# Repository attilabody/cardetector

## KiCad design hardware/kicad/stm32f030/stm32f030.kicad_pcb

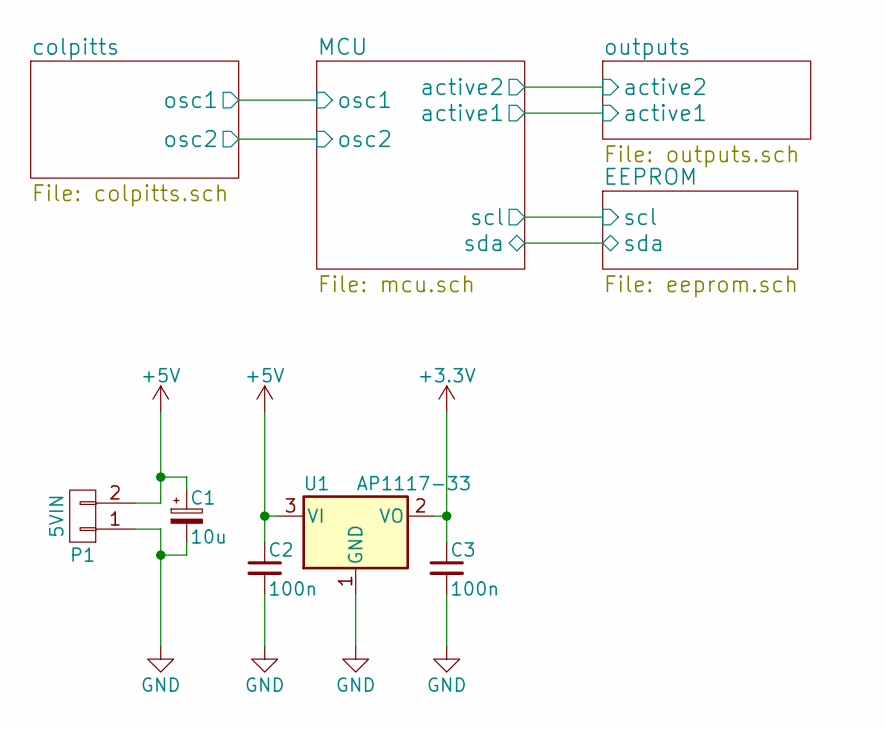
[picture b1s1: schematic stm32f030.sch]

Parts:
C1: 10u; Tantalum_Case-B_EIA-3528-21_Hand
C2, C3: 100n; C_0805_HandSoldering
P1: 5VIN; bornier2
U1: AP1117-33; SOT-223-3Lead_TabPin2

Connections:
+3V3: C3.1, U1.2 (VO); also elsewhere on the board
+5V: C1.1, C2.1, P1.2, U1.3 (VI); also elsewhere on the board
GND: C1.2, C2.2, C3.2, P1.1, U1.1 (GND); also elsewhere on the board

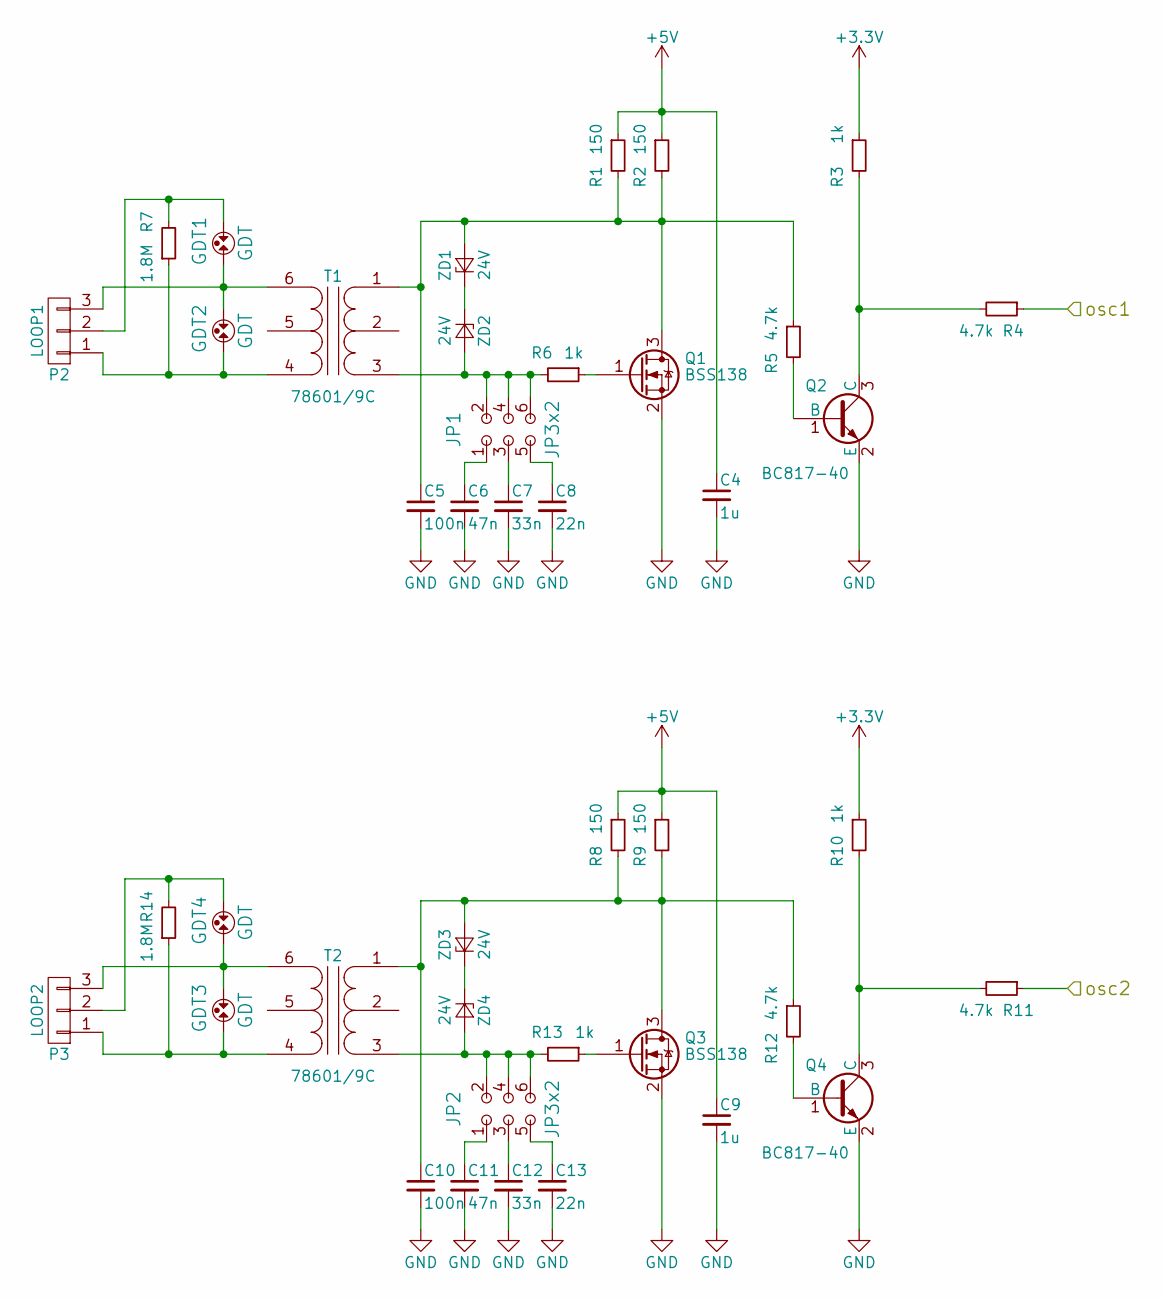
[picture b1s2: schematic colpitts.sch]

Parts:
C4, C9: 1u; C_1206_HandSoldering
C5, C10: 100n; C_1206_HandSoldering
C6, C11: 47n; C_1206
C7, C12: 33n; C_0805_HandSoldering
C8, C13: 22n; C_0805_HandSoldering
GDT1, GDT2, GDT3, GDT4: GDT
JP1, JP2: JP3x2; Pin_Header_Straight_2x03_Pitch2.54mm
P2: LOOP1; bornier3
P3: LOOP2; bornier3
Q1, Q3: BSS138; SOT-23
Q2, Q4: BC817-40; SOT-23
R1, R2, R8, R9: 150; R_0805
R3, R6, R10, R13: 1k; R_0603_HandSoldering
R4, R5, R11, R12: 4.7k; R_0603_HandSoldering
R7, R14: 1.8M; R_0603_HandSoldering
T1, T2: 78601/9C; Murata_Impulse_Transformer
ZD1, ZD2, ZD3, ZD4: 24V; D_MiniMELF_Standard

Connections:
+3V3: R3.1, R10.1; also elsewhere on the board
+5V: C4.1, C9.1, R1.1, R2.1, R8.1, R9.1; also elsewhere on the board
/MCU/osc1: R4.1; also elsewhere on the board
/MCU/osc2: R11.1; also elsewhere on the board
GND: C4.2, C5.2, C6.2, C7.2, C8.2, C9.2, C10.2, C11.2, C12.2, C13.2, Q1.2 (S), Q2.2 (E), Q3.2 (S), Q4.2 (E); also elsewhere on the board
unnamed: C5.1, Q1.3 (D), R1.2, R2.2, R5.1, T1.1 (AA), ZD1.2 (A)
unnamed: C6.1, JP1.1
unnamed: C7.1, JP1.3
unnamed: C8.1, JP1.5
unnamed: C10.1, Q3.3 (D), R8.2, R9.2, R12.1, T2.1 (AA), ZD3.2 (A)
unnamed: C11.1, JP2.1
unnamed: C12.1, JP2.3
unnamed: C13.1, JP2.5
unnamed: GDT1.1, GDT2.2, P2.3, T1.6 (SB)
unnamed: GDT1.2, P2.2, R7.2
unnamed: GDT2.1, P2.1, R7.1, T1.4 (SA)
unnamed: GDT3.1, P3.1, R14.1, T2.4 (SA)
unnamed: GDT3.2, GDT4.1, P3.3, T2.6 (SB)
unnamed: GDT4.2, P3.2, R14.2
unnamed: JP1.2, JP1.4, JP1.6, R6.2, T1.3 (AB), ZD2.2 (A)
unnamed: JP2.2, JP2.4, JP2.6, R13.2, T2.3 (AB), ZD4.2 (A)
unnamed: Q1.1 (G), R6.1
unnamed: Q2.1 (B), R5.2
unnamed: Q2.3 (C), R3.2, R4.2
unnamed: Q3.1 (G), R13.1
unnamed: Q4.1 (B), R12.2
unnamed: Q4.3 (C), R10.2, R11.2
unnamed: ZD1.1 (K), ZD2.1 (K)
unnamed: ZD3.1 (K), ZD4.1 (K)

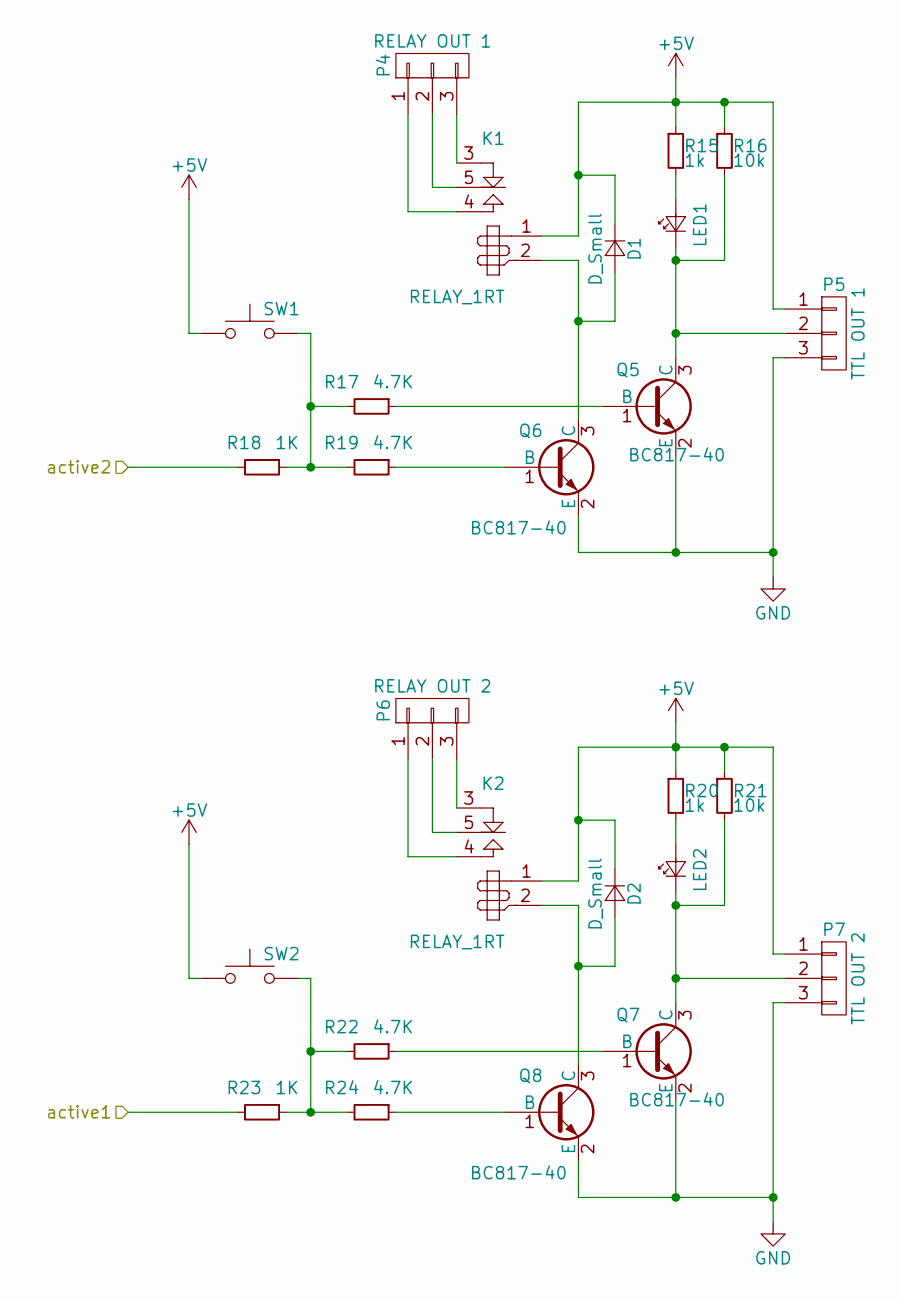
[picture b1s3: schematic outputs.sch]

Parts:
D1, D2: D_Small; D_MiniMELF_Standard
K1, K2: RELAY_1RT; SRD-SL-C
LED1, LED2: LED_Small; LED_0805
P4: RELAY OUT 1; bornier3
P5: TTL OUT 1; Pin_Header_Straight_1x03_Pitch2.54mm
P6: RELAY OUT 2; bornier3
P7: TTL OUT 2; Pin_Header_Straight_1x03_Pitch2.54mm
Q5, Q6, Q7, Q8: BC817-40; SOT-23_Handsoldering
R15, R20: 1k; R_0603_HandSoldering
R16, R21: 10k; R_0603_HandSoldering
R17, R19, R22, R24: 4.7K; R_0603_HandSoldering
R18, R23: 1K; R_0603_HandSoldering
SW1, SW2: SW_Push; TS_362

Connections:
+5V: D1.1 (K), D2.1 (K), K1.1, K2.1, P5.1, P7.1, R15.1, R16.1, R20.1, R21.1, SW1.1, SW2.1; also elsewhere on the board
/MCU/active1: R23.2; also elsewhere on the board
/MCU/active2: R18.2; also elsewhere on the board
GND: P5.3, P7.3, Q5.2 (E), Q6.2 (E), Q7.2 (E), Q8.2 (E); also elsewhere on the board
unnamed: D1.2 (A), K1.2, Q6.3 (C)
unnamed: D2.2 (A), K2.2, Q8.3 (C)
unnamed: K1.3 (R1), P4.3
unnamed: K1.4 (T1), P4.1
unnamed: K1.5 (C1), P4.2
unnamed: K2.3 (R1), P6.3
unnamed: K2.4 (T1), P6.1
unnamed: K2.5 (C1), P6.2
unnamed: LED1.1 (K), P5.2, Q5.3 (C), R16.2
unnamed: LED1.2 (A), R15.2
unnamed: LED2.1 (K), P7.2, Q7.3 (C), R21.2
unnamed: LED2.2 (A), R20.2
unnamed: Q5.1 (B), R17.1
unnamed: Q6.1 (B), R19.1
unnamed: Q7.1 (B), R22.1
unnamed: Q8.1 (B), R24.1
unnamed: R17.2, R18.1, R19.2, SW1.2
unnamed: R22.2, R23.1, R24.2, SW2.2

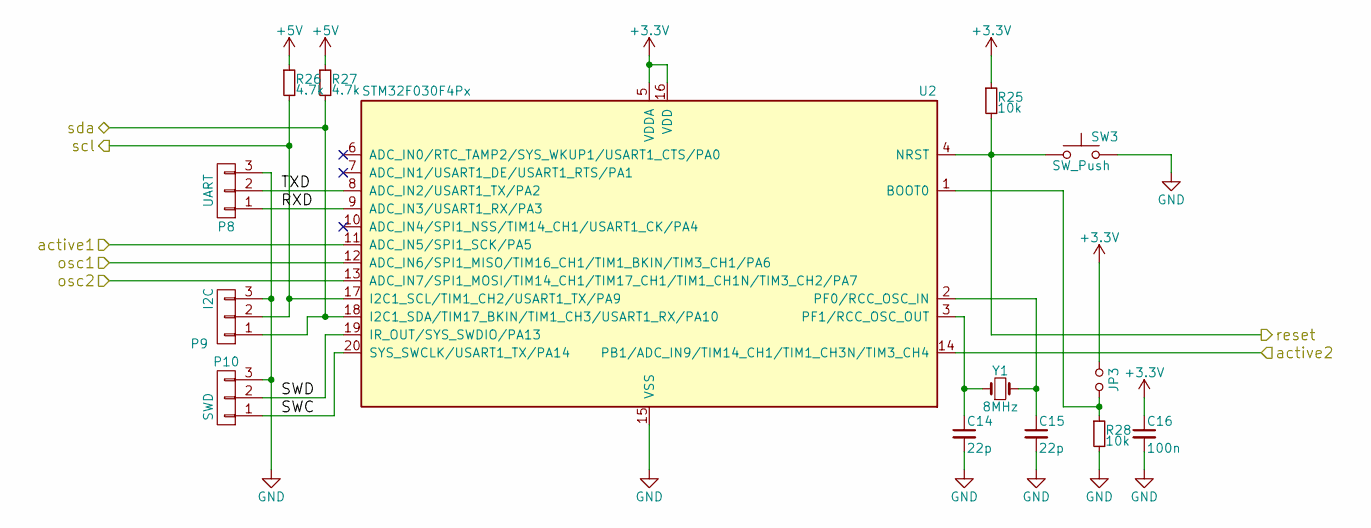
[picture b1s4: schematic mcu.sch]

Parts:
C14, C15: 22p; C_0603_HandSoldering
C16: 100n; C_0805_HandSoldering
JP3: boot0; Pin_Header_Straight_1x02_Pitch2.54mm
P8: UART; Pin_Header_Straight_1x03_Pitch2.54mm
P9: I2C; Pin_Header_Straight_1x03_Pitch2.54mm
P10: SWD; Pin_Header_Straight_1x03_Pitch2.54mm
R25, R28: 10k; R_0603_HandSoldering
R26, R27: 4.7k; R_0603_HandSoldering
SW3: SW_Push; TS_362
U2: STM32F030F4Px; TSSOP-20_4.4x6.5mm_Pitch0.65mm_Handsoldering
Y1: 8MHz; Crystal_HC49-4H_Vertical

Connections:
+3V3: C16.1, JP3.1, R25.1, U2.5 (VDDA), U2.16 (VDD); also elsewhere on the board
+5V: R26.1, R27.1; also elsewhere on the board
/EEPROM/scl: P9.2, R26.2, U2.17 (I2C1_SCL/TIM1_CH2/USART1_TX/PA9); also elsewhere on the board
/EEPROM/sda: P9.1, R27.2, U2.18 (I2C1_SDA/TIM17_BKIN/TIM1_CH3/USART1_RX/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); also elsewhere on the board
/MCU/RXD: P8.1, U2.9 (ADC_IN3/USART1_RX/PA3)
/MCU/SWC: P10.1, U2.20 (SYS_SWCLK/USART1_TX/PA14)
/MCU/SWD: P10.2, U2.19 (IR_OUT/SYS_SWDIO/PA13)
/MCU/TXD: P8.2, U2.8 (ADC_IN2/USART1_TX/PA2)
/MCU/active1: U2.11 (ADC_IN5/SPI1_SCK/PA5); also elsewhere on the board
/MCU/active2: U2.14 (PB1/ADC_IN9/TIM14_CH1/TIM1_CH3N/TIM3_CH4); also elsewhere on the board
/MCU/osc1: U2.12 (ADC_IN6/SPI1_MISO/TIM16_CH1/TIM1_BKIN/T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); also elsewhere on the board
/MCU/osc2: U2.13 (ADC_IN7/SPI1_MOSI/TIM14_CH1/TIM17_CH1/T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); also elsewhere on the board
/MCU/reset: R25.2, SW3.1, U2.4 (NRST)
GND: C14.2, C15.2, C16.2, P8.3, P9.3, P10.3, R28.2, SW3.2, U2.15 (VSS); also elsewhere on the board
unnamed: C14.1, U2.3 (PF1/RCC_OSC_OUT), Y1.1
unnamed: C15.1, U2.2 (PF0/RCC_OSC_IN), Y1.2
unnamed: JP3.2, R28.1, U2.1 (BOOT0)

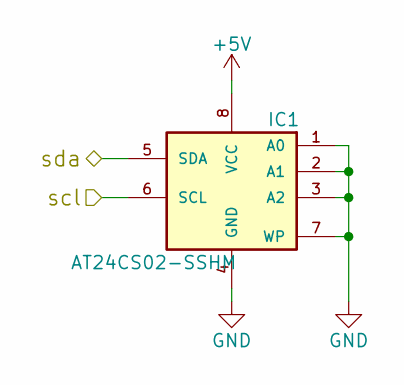
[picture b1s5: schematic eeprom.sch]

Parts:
IC1: AT24CS02-SSHM; SOIC-8_3.9x4.9mm_Pitch1.27mm

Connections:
+5V: IC1.8 (VCC); also elsewhere on the board
/EEPROM/scl: IC1.6 (SCL); also elsewhere on the board
/EEPROM/sda: IC1.5 (SDA); also elsewhere on the board
GND: IC1.1 (A0), IC1.2 (A1), IC1.3 (A2), IC1.4 (GND), IC1.7 (WP); also elsewhere on the board

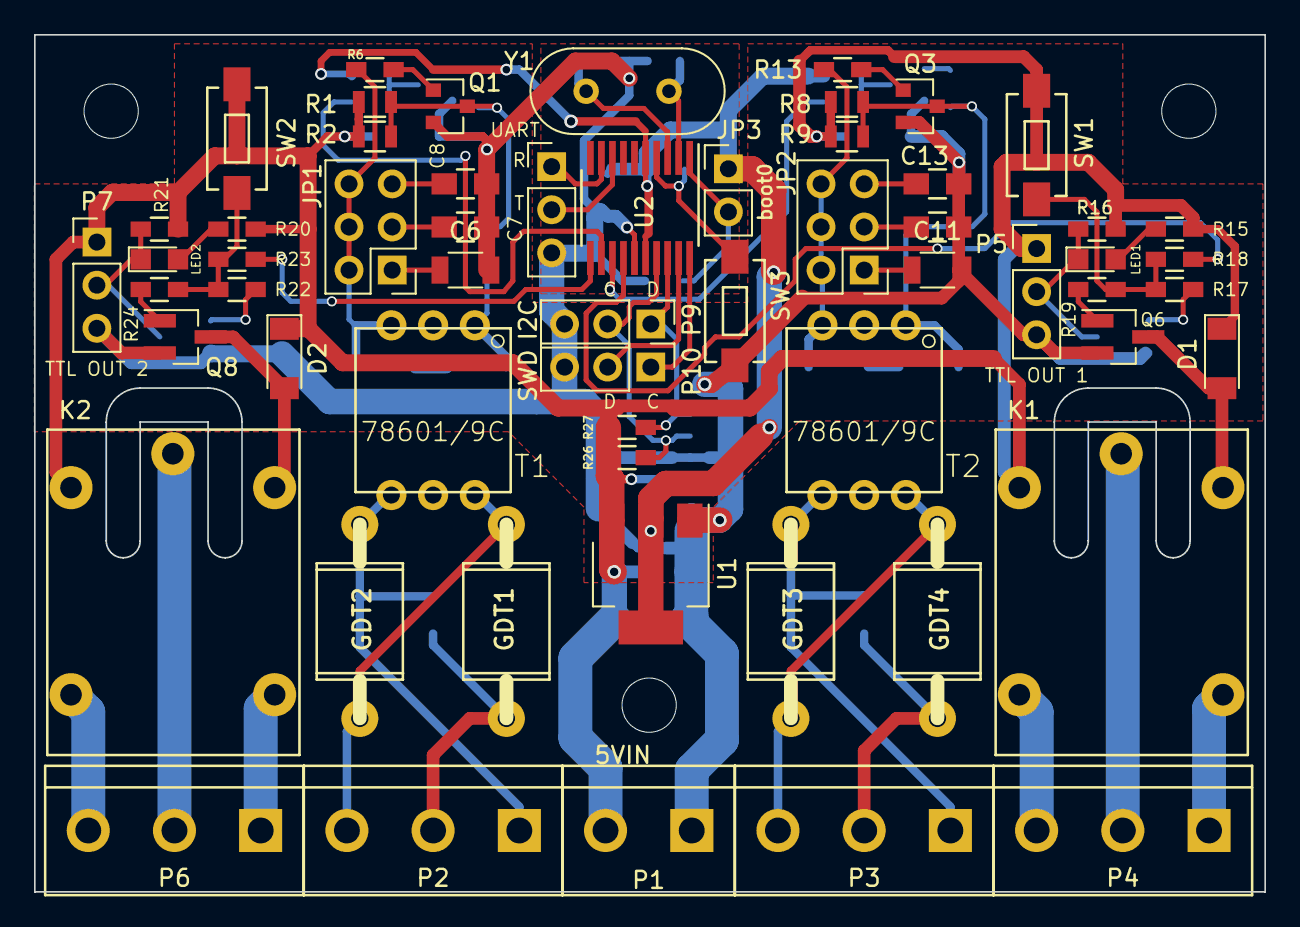
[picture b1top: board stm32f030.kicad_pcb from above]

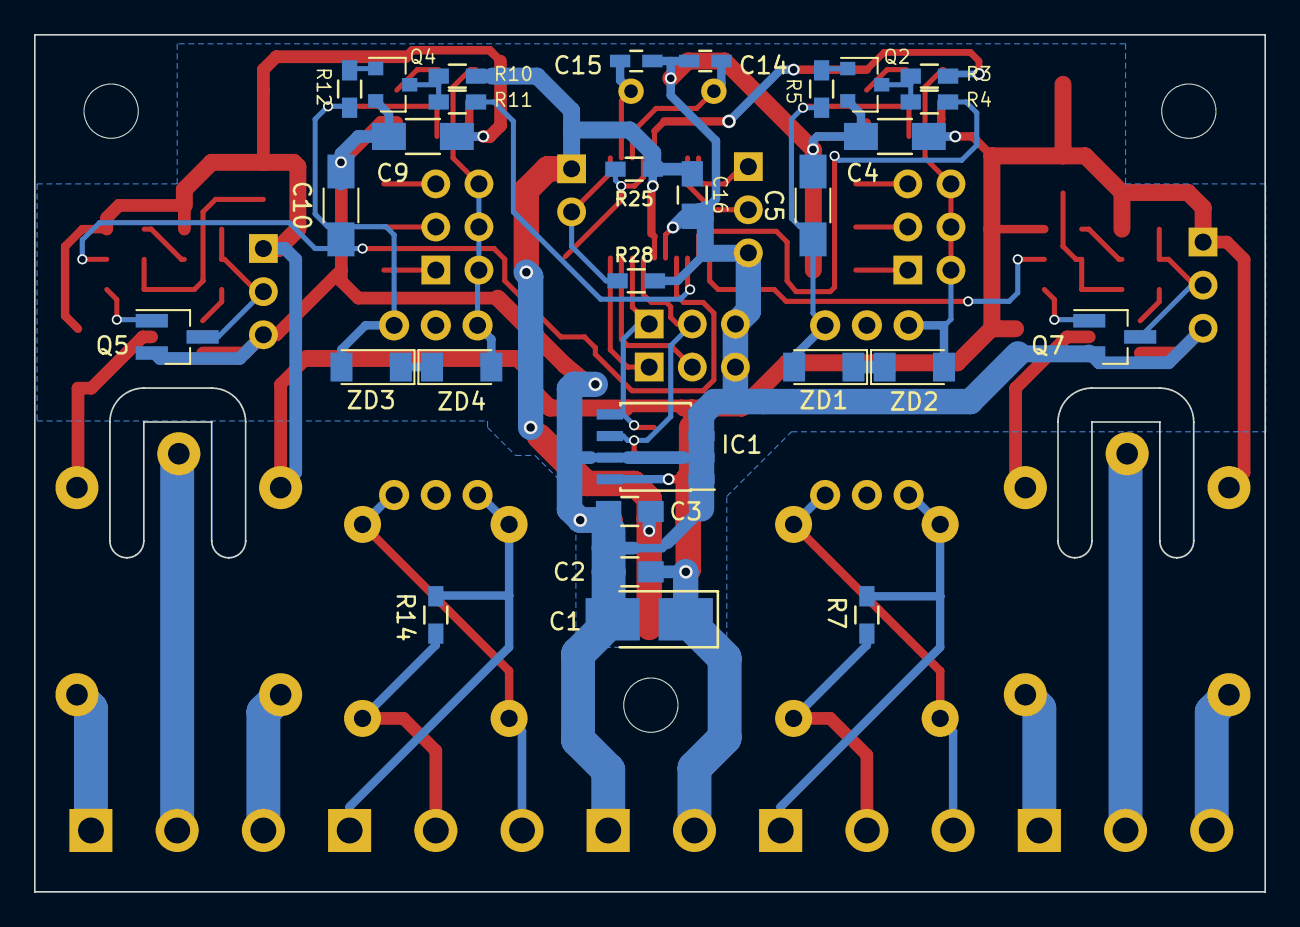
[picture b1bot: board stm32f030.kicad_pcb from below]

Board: 2 copper layers, 72.5 x 50.5 mm, 88 parts (29 on the bottom side), 59 nets.

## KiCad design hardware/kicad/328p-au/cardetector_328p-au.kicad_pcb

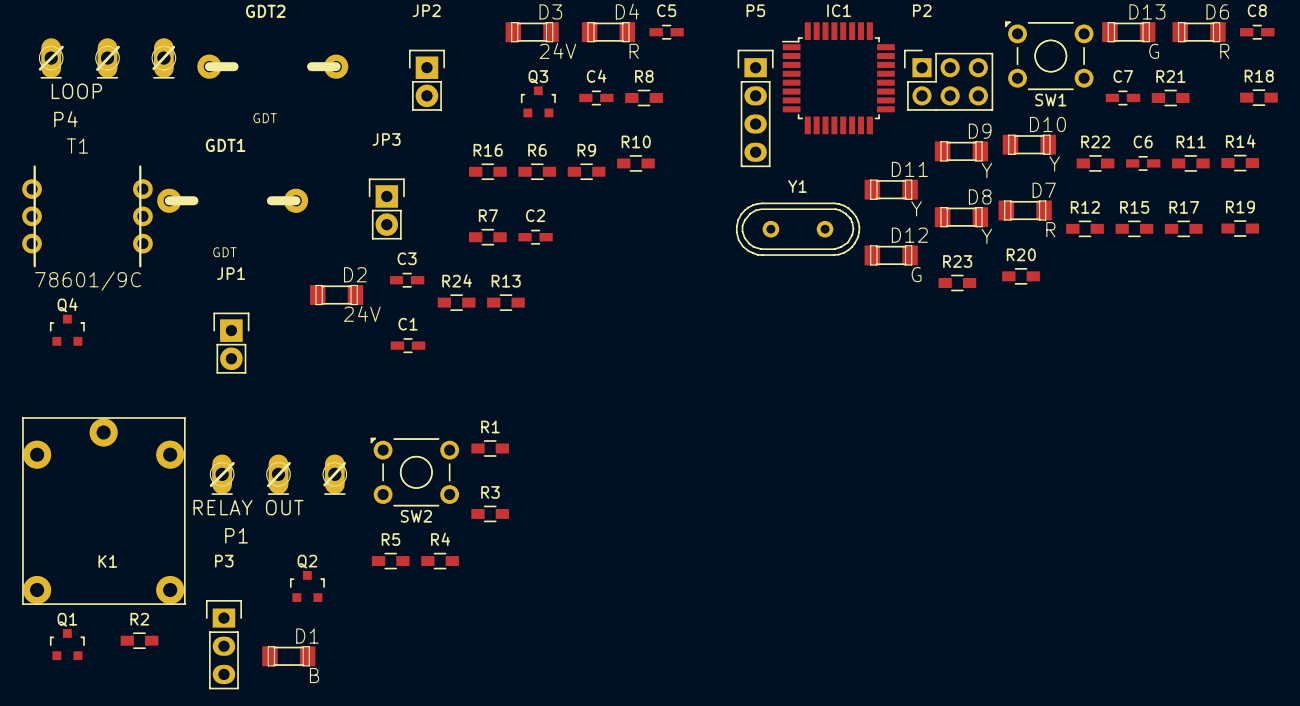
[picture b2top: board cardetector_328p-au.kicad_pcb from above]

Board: 2 copper layers, 64 parts (0 on the bottom side), 50 nets, no tracks yet.

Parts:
C1: 100n; C_0603_HandSoldering
C2: 47n; C_0603_HandSoldering
C3: 33n; C_0603_HandSoldering
C4: 22n; C_0603_HandSoldering
C5, C6: 1u; C_0603_HandSoldering
C7, C8: 22p; C_0603_HandSoldering
D1: B; SOD80C
D2, D3: 24V; SOD80C
D4, D6, D7: R; SOD80C
D8, D9, D10, D11: Y; SOD80C
D12, D13: G; SOD80C
GDT1, GDT2: GDT; CG5350L
IC1: ATMEGA328-A; TQFP-32_7x7mm_Pitch0.8mm
JP1, JP2, JP3: Jumper_NO_Small; Pin_Header_Straight_1x02
K1: RELAY_1RT; SRD-SL-C
P1: RELAY OUT; W237-133
P2: ISP; Socket_Strip_Straight_2x03
P3: TTL OUT; Pin_Header_Straight_1x03
P4: LOOP; W237-133
P5: I2C; Pin_Header_Straight_1x04
Q1, Q2, Q4: BC817-40; SOT-23
Q3: BSS138; SOT-23
R1: 1K; R_0603_HandSoldering
R2, R3: 4.7K; R_0603_HandSoldering
R4, R7, R11, R12, R13, R15, R16, R17, R18, R19, R20, R21: 1k; R_0603_HandSoldering
R5, R14, R22, R23: 10k; R_0603_HandSoldering
R6: 1.8M; R_0603_HandSoldering
R8, R9: 150; R_0603_HandSoldering
R10, R24: 4.7k; R_0603_HandSoldering
SW1, SW2: TACTILE_SW; SW_TH_Tactile_Omron_B3F-10xx
T1: 78601/9C; 78601_9C
Y1: 16MHz; Crystal_HC49-U_Vertical

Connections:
+5V: C5.1, C6.1, D4.2, IC1.4, IC1.6, IC1.18, K1.1, P2.2, P3.1, P5.2, R4.1, R5.1, R8.1, R9.1, R13.1, R22.1, R23.1, SW2.1, SW2.2
/coplpitts/osc: IC1.2, R24.1
/output/active: IC1.12, R1.2
Earth: GDT2.2, P4.2, R6.2
GND: C1.2, C2.2, C3.2, C4.2, C5.2, C6.2, C7.2, C8.2, D6.1, D7.1, D8.1, D9.1, D10.1, D11.1, D12.1, D13.1, IC1.3, IC1.5, IC1.21, P2.6, P3.3, P5.1, Q1.2, Q2.2, Q3.2, Q4.2, R14.1, R16.2, SW1.1, SW1.2
unnamed: C1.1, D2.2, Q3.3, R8.2, R9.2, R10.1, T1.6
unnamed: C2.1, JP1.2
unnamed: C3.1, JP2.2
unnamed: C4.1, JP3.2
unnamed: C7.1, IC1.8, Y1.1
unnamed: C8.1, IC1.7, Y1.2
unnamed: D1.1, P3.2, Q2.3, R5.2
unnamed: D1.2, R4.2
unnamed: D2.1, D3.1
unnamed: D3.2, JP1.1, JP2.1, JP3.1, R7.2, T1.4
unnamed: D4.1, R16.1
unnamed: D6.2, R11.2
unnamed: D7.2, R12.2
unnamed: D8.2, R21.2
unnamed: D9.2, R20.2
unnamed: D10.2, R19.2
unnamed: D11.2, R18.2
unnamed: D12.2, R17.2
unnamed: D13.2, R15.2
unnamed: GDT1.1, P4.3, T1.1
unnamed: GDT1.2, GDT2.1, P4.1, R6.1, T1.3
unnamed: IC1.10, R20.1
unnamed: IC1.11, R21.1
unnamed: IC1.13, R12.1
unnamed: IC1.14, R11.1
unnamed: IC1.15, P2.4
unnamed: IC1.16, P2.1
unnamed: IC1.17, P2.3
unnamed: IC1.23, R15.1
unnamed: IC1.24, R17.1
unnamed: IC1.25, R18.1
unnamed: IC1.26, R19.1
unnamed: IC1.27, P5.3, R22.2, R23.2
unnamed: IC1.28, P5.4
unnamed: IC1.29, P2.5, R14.2, SW1.3, SW1.4
unnamed: K1.2, Q1.3
unnamed: K1.3, P1.3
unnamed: K1.4, P1.1
unnamed: K1.5, P1.2
unnamed: Q1.1, R3.1
unnamed: Q2.1, R2.1
unnamed: Q3.1, R7.1
unnamed: Q4.1, R10.2
unnamed: Q4.3, R13.2, R24.2
unnamed: R1.1, R2.2, R3.2, SW2.3, SW2.4

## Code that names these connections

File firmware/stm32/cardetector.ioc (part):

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Mcu.Name=STM32F030F4Px
Mcu.Package=TSSOP20
Mcu.UserName=STM32F030F4Px
PA10.Mode=I2C
PA10.Signal=I2C1_SDA
PA13.Mode=Serial_Wire
PA13.Signal=SYS_SWDIO
PA14.Mode=Serial_Wire
PA14.Signal=SYS_SWCLK
PA2.Mode=Asynchronous
PA2.Signal=USART1_TX
PA3.Mode=Asynchronous
PA3.Signal=USART1_RX
PA5.GPIOParameters=GPIO_Label
PA5.GPIO_Label=ACTIVE1
PA5.Signal=GPIO_Output
PA6.GPIOParameters=GPIO_Label
PA6.GPIO_Label=OSC1
PA6.Signal=S_TIM16_CH1
PA7.GPIOParameters=GPIO_Label
PA7.GPIO_Label=OSC2
PA7.Signal=S_TIM17_CH1
PA9.Mode=I2C
PA9.Signal=I2C1_SCL
PB1.GPIOParameters=GPIO_Label
PB1.GPIO_Label=ACTIVE2
PB1.Signal=GPIO_Output
PF0-OSC_IN.Mode=HSE-External-Oscillator
PF0-OSC_IN.Signal=RCC_OSC_IN
PF1-OSC_OUT.Mode=HSE-External-Oscillator
PF1-OSC_OUT.Signal=RCC_OSC_OUT
RCC.SYSCLKFreq_VALUE=48000000
RCC.SYSCLKSource=RCC_SYSCLKSOURCE_PLLCLK
board=cardetector

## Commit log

2016-04-29 cardetector: initial commit
2016-05-14 serial output for debugging
2016-05-14 using timer0 instead of timer1
2016-05-14 continous counter opeartion
2016-05-14 average
2016-05-14 first it-may-even-work version
2016-05-16 serial code embedded only when absolutely necessary; params struct, function provided to read them from eeprom timelimit interpreted in seconds (4 samples) instead of samples
2016-05-18 Pins and timers selected in config.h (cardetector.c became model independent) Separate pin for signaling and LED
2016-05-22 Rejoining 328p and tiny85 code
2016-05-26 detection fine-tuning
2016-05-29 detector shamatics added
2016-05-29 hardware: replaced impulse transformer, VCC capacitors added
2016-05-29 fixing TIFR T0 overflow interrupt pending bit reset (0->1)
2016-06-02 adding bidirectional diff shift feature (right shift on negative values)
2016-06-02 hardware: separate pages for analog and digital part, separate schematics for tiny85 and mega328p
2016-06-02 hardware: t85 board fuckery
2016-06-02 hardware: t85 all parts on the board
2016-06-02 hardware-t85: almost there
2016-06-02 hardware: separate DIP and SIL drawings for mega328p, gitignore tuning
2016-06-02 hardware: renamed schs to reflect the CPU (variant) used.
2016-06-03 hardware-t85: really almost there
2016-06-04 hardware-m328p-au: preparing schematics for board creation
2016-06-05 hardware-m328p-pu: board created
2016-06-05 hardware-m328p-au: MCU referred from gate433.lbr
2016-06-05 hardware-328p-au: more smt replacements
2016-06-08 Board level 0
2016-06-10 detector328p-au level 1: devices at place
2016-06-11 detector328p-au almost wired
2016-06-11 detector328p-au wiring ready, labels need fixing
2016-06-11 detector328p-au final
2016-06-11 detector328p-au serial port
2016-06-11 detector328p-au R2->1K, T1->BC817
2016-06-12 hardware: eagle files moved from hardware/ to hardware/eagle/ .gitignore prepared for kicad files
2016-06-13 detector_t85-pu: T2 10K pull-up, Zener 5,1V -> 20V
2016-06-13 hardware/kicad/328p-au: schematic created
2016-06-13 hardware/kicad/328p-au: separated output sheet
2016-06-14 hardware/kicad/328p-au: separated collpits page, footprints assigned and imported to PCB
2016-06-19 hardware/kicad/328p-au: use 3x2 jumper block for frequency selection
2016-06-19 cardetector: i2c handler, dead code elimination
2016-06-20 cardetector: PCF8574 I/O extender
2016-06-22 cardetector: i2c LCD
2016-06-24 hardware/eagle: added 3 push buttons
2016-06-24 hardware/kicad: added serial connector && 3 push buttons
2016-06-24 CarDetector v1.1 hardware (3 more button)
2016-06-25 Interrupt driven serial communication proto
2016-06-25 atmel studio project files
2016-06-27 serial commands
2016-06-28 serial command: show
2016-07-01 cardetector: parameter tuning over serial console
2016-07-02 cardetector: parallel build, serial code #ifdefs
2016-07-04 Fix: detector_t85-pu: T2 10K pull-up, Zener 5,1V -> 20V
2016-07-10 cardetector: refactoring, led bar implementation
2016-07-13 cardetector: serial debug on/of
2016-07-15 cardetector: added Makefile
2016-07-23 C1: 1206; C2,C3,C4: 0805; Power polarity signs
2016-07-24 cardetector: WDT
2017-01-22 Atmel firmware moved to subfolder
2017-01-22 added stm32 firmware
2017-01-23 hardware/kicad/stm32f030: created
2017-01-24 hardware/kicad/stm32f030: progress
2017-01-28 hardware/kicad/stm32f030: modules ready
2017-01-30 stm32 debugger config
2017-01-31 slight;y modified module layout
2017-01-31 more optimizations on modules
2017-01-31 space for mounting hole
2017-02-02 PCB V0.90
2017-02-02 hardware/kicad: all LED IDs moved to the board area and made visible
2017-02-09 hardware/kicad/stm32f030: adding eeprom step1
2017-02-09 hardware/kicad/stm32f030: adding eeprom step2
2017-02-10 hardware/kicad/stm32f030: adding eeprom step3
2017-02-13 hardware/kicad/stm32f030: final touches
2017-02-14 hardware/kicad/stm32f030: i2c eeprom pad widening
2017-02-14 firmware/stm32: moved component initialization codes to separate c/h files
2017-02-14 firmware/stm32 f030f4Px firmware code moved to separate subfolder
2017-02-14 hardware/kicad/stm32f030: use upper layer zones for power
2017-02-15 hardware/kicad: cardetector.pretty moved from stm32f030 to ..
2017-02-15 hardware/kicad: stm32f103 created (stm32f030 copy)
2017-02-19 hardware/kicad/stm32f103: MCU/LED block ready
2017-02-21 hardware/kicad/stm32f103: Almost there...
2017-02-23 hardware/kicad/stm32f103: Minor cosmetic changes
2017-02-23 hardware/kicad/stm32f030: Ledbar removed, reorg started
2017-02-25 hardware/kicad/stm32f030: blocks ready
2017-02-28 hardware/kicad/stm32f030: everything is connected, DRC OK
2017-03-01 hardware/kicad/stm32f030: removed derecated libraries
2017-03-01 firmware/stm32/F103C8Tx firmware added
2017-03-05 firmware/stm32: renamed 103 and 030 projects
2017-03-05 firmware/stm32: i2cmaster, pcf8574, i2clcd added to cardetector_common
2017-03-05 hardware/kicad/stm32f030: changed i2c bus and eeprom voltage to 5V
2017-03-05 firmware/stm32/f030f4px: i2clcd and usart send test
2017-03-11 firmware/stm32/f030f4px: detection working
2017-03-12 firmware/stm32/cardetector_common fixes and improvements
2017-03-12 firmware/stm32 cardetector_common renamed to stm32plus, i2cmaster modularized i2ceeprom seems to work
2017-03-14 firmware/stm32/stm32plus: removed m_ prefixes, optimized i2clcd init
2017-03-17 firmware/stm32/F030F4Px Almost feature complete (only MCP23017 led bar missing, pcf8574 led bar untested)
2017-09-22 firmware/stm32/F030F4Px migrated to new cube && sw4stm32 versions iwdg switched on (code still should be written to work)
2017-09-22 firmware/stm32/F030F4Px: fine-tuning USE_ flag usage
2017-09-22 hardware/kicad/stm32f030: kicad version && lib bump
2017-09-27 stm32f030 PCB text fixes
2017-09-28 Atmel firmware serial buffer size (theoretical) bug fix
2017-10-01 st: various minor fixes
2017-10-02 barechip-F030F4Px added (board test)
2017-10-03 Removing accidentally added backup files
2017-10-03 kicad/stm32f030: corrected board size
2017-10-06 ST firmware usart library changes
2017-10-06 firmware/stm32/barechip-F030F4Px chagnes
2017-10-06 STM32F030F4Px firmware adoption to proto board implementation
2017-10-08 Made lcd/ledbar mutually exclusive again (too much effort to make them work parallel and would not fit to 030f4
2017-10-08 ledbar values from config
2017-10-23 STM32f030F4Px V0.99
2017-10-23 kicad-STM32F030 modifications during test batch assembly
2017-12-05 checked in last state of firmware/stm32/barechip test project
2018-01-26 stm32plus: extern "C" into the headers for mixed projects
2018-01-26 STM32F030F4Px: copied Drivrers/uart.c into Application folder to protect from overwriting by CubeMX
2018-04-12 Added licecse
2019-07-16 Making to compile with newer SW4STM32 version
2019-07-20 Rebuilt project structure
